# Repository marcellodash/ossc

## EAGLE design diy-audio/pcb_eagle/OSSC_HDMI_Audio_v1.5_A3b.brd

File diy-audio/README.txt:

########################################################################
# IMPORTANT NOTE:                                                      #
#                                                                      #
# This branch is not longer updated. marqs85 has included the firmware #
# adaptations needed for this mod into the release branch. Hence I     #
# started a new repository just for the AddOn-PCB.                     #
# You can find it here: https://github.com/borti4938/Audio4OSSC        #
########################################################################

The OSSC does not output audio over HDMI or DVI-D, respectively. This add on captures the analoge audio you feed over the SCART or audio 3.5mm stereo jack. The audio signal is digitalize and put into the IT6613E over the I2S audio interface.

Firmware
========
The IT6613E has to be programmed appropriately to insert audio to the digital video output. In the 'original' firmware audio is not taken into account. Therefore the firmware of the OSSC has to be updated.
You can grab the current firmware here: https://github.com/borti4938/ossc/tree/diy-audio/diy-audio/fw-build
I do my best to keep the firmware synchronized with updates by marqs85. However, as marqs includes more and more features to the firmware there might be a point where I have to cut features due to the lack of memory space.

PCB Production
==============
Choose the service you would ever like. I have uploaded the design to OSHPark, too.
VERY IMPORTANT: The substrate thickness has to be as thin as possible.
The PCB is design to sit between lifted pins of the IT6613 (the HDMI transmitter) and OSSC-PCB. Just look at the installation pictures to get an idea ;)
I have produced the PCBs with OSHPark and have chosen 0.8mm thickness. The PCB must not be thicker.
Link to PCB at OSHPark:
- https://oshpark.com/shared_projects/4u6ta1CE (for v1.3)
- https://oshpark.com/shared_projects/1sT4vN4I (for v1.5)
- https://oshpark.com/shared_projects/bOskL1g1 (for v1.5 with wired connection to the SCART)

Part list of the DIY-Audio PCB
==============================
running number ------ footprint(s) --------- device/part --------- package ----- mouser ordering key
     01         |  U1                 |  PCM1808               |  TSSOP14     |  595-PCM1808PWR
     02         |  U2                 |  74LVC1G34             |  SOT23-5     |  595-SN74LVC1G34DCKR
     03         |  U3                 |  MK2705SLF             |  SOIC8       |  972-MK2705SLF
     04         |  FB1, FB2           |  Ferrit Beat           |  SMD0603     |  81-BLM18PG471SN1D
     05         |  C1                 |  tantal-cap. 47uF/16V  |  SMD case C  |  74-293D476X9016C2TE3
     06         |  R11, R12           |  res. >2.2 kOhm        |  SMD0603     |  71-CRCW06034K99FKEAH (e.g. 4.99k)
     07         |  C11, C13, C15      |  tantal-cap. 10uF/6.3V |  SMD case A  |  74-TR3A106M6R3C1500
     08         |  C12, C14, C16, C21 | cap. 0.1uF/50V         |  SMD0603     |  77-VJ0603V104MXACBC
     09         |  C17, C18, C31      | tantal-cap. 1uF/16V    |  SMD case A  |  74-293D105X9016A2TE3
     10         |  R19, R20           | res. ***               |  SMD0603     |  see description below
     11         |  C19, C20           | cap. ***               |  SMD0603     |  see description below
     12         |  R31                | res. 33 Ohm            |  SMD0603     |  71-CRCW060333R0FKEAH
     13         |  C32, C33           | cap. 0.01uF/50V        |  SMD0603     |  77-VJ0603Y103KXACBC

RC-filtering of the Audio
=========================
The RC filters (R19,C19) and (R20,C20) mainly bandlimits the noise. The filter also avoids aliasing effects if the bandwith of the audio signal increases.
The PCM1808 samples the audio signal with 96kHz. This means that the cut-off frequency of the filters have to be 96kHz or below. The firmware will also allows you to further downsample the datastream to 48kHz. If you want to use that I recommend you to set the filter to 48kHz or below to avoid aliasing.
The cut-off frequency f_c of a simple RC low pass filter is determined by f_c = 1/(2*pi*R*C).
here is my choice which gives a cut-off frequency of 47.938kHz.
     10         |  R19, R20  |  res. 3.32 kOhm   |  SMD0603  |  71-CRCW0603-3.32K-E3  
     11         |  C19, C20  |  cap. 1000pF/50V  |  SMD0603  |  77-VJ0603Y102KXACBC

PCB-Installation
=================
(see pictures; assumes that at least the SCART connector has been desoldered)
01 - v1.3 - bend up pins 9, 10 and 11 of the IT6613 (v1.3 only!!!) (and eventually pin 5 - see External MCLK)
   - v1.5 - cut three wires between each pair of solder joints marked with I2S, WS and SCK (v1.5 only) (eventually lift pin 5 of the IT6613E - see External MCLK)
02 - make a placement check (might look different between v1.3 and v1.5)
03 - cut off the plastic around pin 2, 4 and 6 of the SCART connector if needed
04 - solder the IT6613 into place (if not done yet) and approximately fix the audio pcb into place (v1.5 does not sit under some pins)
05 - solder the SCART plug into place and solder the audio PCB onto the SCART connector (remind to check the pin assignment at the IT6613 during soldering the first leg)
06 - v1.3 - solder pin 9, 10 and 11 of the IT6613 onto the audio PCB (v1.3 only)
   - v1.5 - solder the three top solder joints on the OSSC PCB (I2S, WS and SCK) to the DIY audio PCB (v1.5 only)
07 - connect the wires
08 - 5V and 3.3V can be get from U5
09 - 27MHz from the crystal oscillator (pin between U7 and U9)
10 - Pin 5 of the IT6613E lifted and connected to R31 (top pad)

External MCLK
=============
The IT6613E derives the system clock for audio processing (audio master clock, MCLK) from the I2S input (I2S0, WS and SCK) by default. It is also possible to feed the MCLK into the IT6613E using pin 5 and setting appropriate register bits.
If you have problems with the internally derived MCLK of the IT6613E, you have to use the external MCLK. Problems mean that you might have audio dropouts or you simply hear nothing! Then you have to use the external MCLK.
Next to setting the option in the OSSC menu you might have to modify your OSSC a bit.
- older audio boards v1.5-A3x, v1.3-A3, and before: lift pin 5 of the IT6613E and connect the pin with R31 (top pad; see picture 10) 
- newer audio boards v1.3-A4: designed to lift pin 5 before installation. Nothing more to done.
- newer audio boards v1.5-A4x: lift pin 5 and connect the pin with the pad 'MCLK' on the audio add-on board

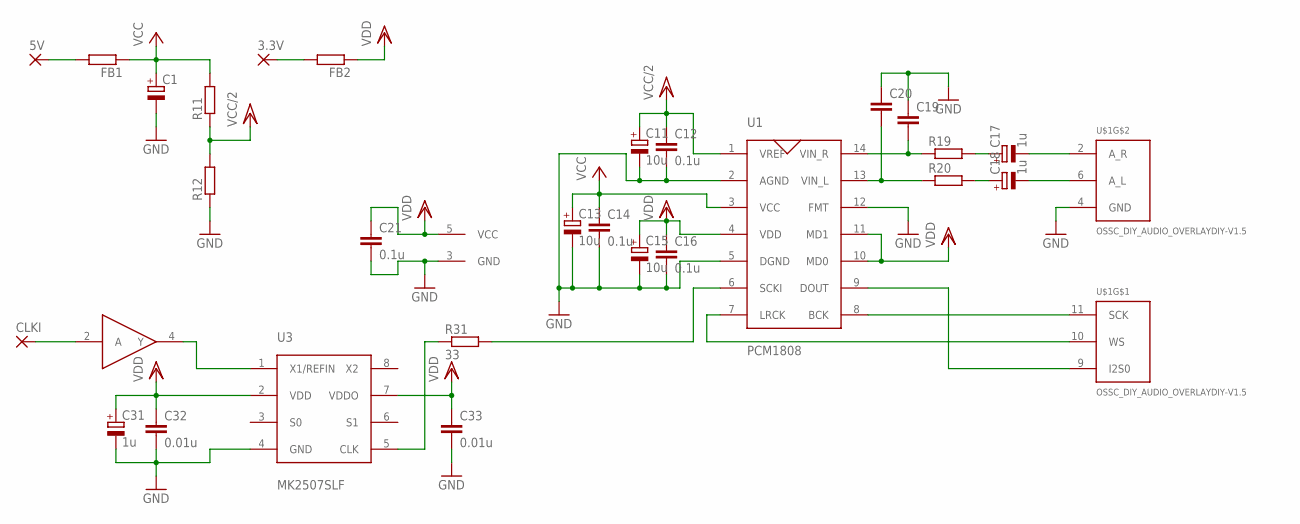
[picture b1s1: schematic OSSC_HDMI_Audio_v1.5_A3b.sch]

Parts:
3.3V, 5V: SMD2; SMD1,27-2,54
C1: CPOL-EUSMCC; SMC_C
C11, C13, C15: 10u; SMC_A
C12, C14, C16, C21: 0.1u; C0603
C17, C18, C31: 1u; SMC_A
C19, C20: C-EUC0603; C0603
C32, C33: 0.01u; C0603
CLKI: SMD2; SMD1,27-2,54
FB1, FB2: R-EU_R0603; R0603
R11, R12, R19, R20: R-EU_R0603; R0603
R31: 33; R0603
U1: PCM1808
U2: 74LVC1G34; 74LVC1G34DCK
U3: MK2507SLF; SOIC8
U$1: OSSC_DIY_AUDIO_OVERLAYDIY-V1.5; OSSC_OVERLAY_V1.5

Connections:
GND: C1.-, C11.-, C12.2, C13.-, C14.2, C15.-, C16.2, C19.1, C20.1, C21.2, C31.-, C32.2, C33.2, R12.1, U1.2 (AGND), U1.5 (DGND), U1.12 (FMT), U2.3 (GND), U3.4 (GND), U$1.4 (GND)
unnamed: C18.-, U$1.6 (A_L)
unnamed: C17.-, U$1.2 (A_R)
unnamed: C17.+, R19.2
unnamed: C19.2, R19.1, U1.14 (VIN_R)
unnamed: C20.2, R20.1, U1.13 (VIN_L)
unnamed: C18.+, R20.2
unnamed: R31.1, U3.5 (CLK)
unnamed: U2.4 (Y), U3.1 (X1/REFIN)
unnamed: CLKI.1, U2.2 (A)
unnamed: 5V.1, FB1.2
unnamed: 3.3V.1, FB2.2
unnamed: U1.7 (LRCK), U$1.10 (WS)
unnamed: U1.8 (BCK), U$1.11 (SCK)
unnamed: U1.9 (DOUT), U$1.9 (I2S0)
unnamed: R31.2, U1.6 (SCKI)
VCC: C1.+, C13.+, C14.1, FB1.1, R11.2, U1.3 (VCC)
VCC/2: C11.+, C12.1, R11.1, R12.2, U1.1 (VREF)
VDD: C15.+, C16.1, C21.1, C31.+, C32.1, C33.1, FB2.1, U1.4 (VDD), U1.10 (MD0), U1.11 (MD1), U2.5 (VCC), U3.2 (VDD), U3.7 (VDDO)

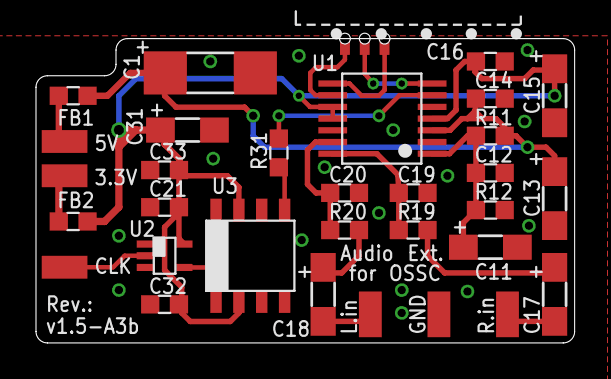
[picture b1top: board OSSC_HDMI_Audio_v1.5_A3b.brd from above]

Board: 2 copper layers, 29.9 x 16.9 mm, 29 parts (0 on the bottom side), 19 nets.

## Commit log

2016-04-26 initial commit diy-audio v0.69
2016-05-22 resort software code database [WIP] - split av_controller.c into several sub-files - WorkInProgress = still needs refactoring
2016-05-30 wrap around some configs
2016-05-30 correct conditional write
2016-05-30 replace some magic numbers
2016-05-31 further replacing of magic numbers
2016-06-23 fw build 0.70-audio (incl. jic file for updating fw using the USB Blaster)
2016-07-08 DIY audio PCB for OSSC v1.5 Side note: The outline of this board (dimension layer) is not tested so far. I don’t have a DIY-v1.5 of the OSSC; just pics. So please give feedback to me for fitting if y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
2016-07-08 change a minor part
2016-07-08 give an idea how installation should look like with v1.5
2016-07-10 fw builds v0.71
2016-08-08 rename PCB files (add ‚A3‘ as on silkscreen)
2016-08-08 Audio Add-On (Version ‚A3b’) with pads for GND and audio (in) allowing installation with wires to the SCART jack. Thanks to Kel for this modification.
2016-08-17 firmware identification on startup (simple a)
2016-08-17 fw build 0.72 for audio add-on
2016-08-18 update read me
2016-08-24 fw 0.72 files
2016-09-12 allow info frames for OSSCs with DVI output in HDMI mode
2016-09-25 External MCLK option to increase compatibility - thanks to Ken (once again ;) ) for testing (and being patient during the tests). There were a lot of others tests before we end up with this solution.
2016-09-25 PCB files with a pad for mclk to IT6613E
2016-11-02 Some adaptations needed for the merge: - preparation for the JP language for the audio menu - removing some (useless) lines
2016-11-18 Last commit: - integrated since fw v0.74 in official releases branch by marqs85 - no upcoming update here - branch left here just as an backup
2016-11-18 Preparation for translation into Japanese
2016-11-18 Resorting menu entries for save settings, reset settings and fw update
2017-01-04 Update projectiles (meaningless commit)
2017-01-09 Outdated note
2017-01-30 External audio clock for it6613 option as alternative build
2017-05-30 resort commands as suggested in programming guide
2017-05-30 Bugfix: audio down-sampling setting
2017-05-30 Setting MCLK adjust command and small bugfix
2017-06-04 Bugfix: screwed up register definitions
2017-06-16 Update gitignore
2017-06-16 Option for audio (ext. mclk) (build option)
2017-08-15 Simple project setting files updated (no functional updates or bugfixes)
2017-10-12 change target mode on loading profile
2017-11-08 bump to Quartus Prime v17.1
2017-11-10 initial commit for automatic LCD backlight control: - hardware driven, software code remains unchanged - BL turned on with any button press (either PCB or RF) - button codes are forwarded to software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
2017-11-10 reduce BL on time down to 3.5s on power cycle
